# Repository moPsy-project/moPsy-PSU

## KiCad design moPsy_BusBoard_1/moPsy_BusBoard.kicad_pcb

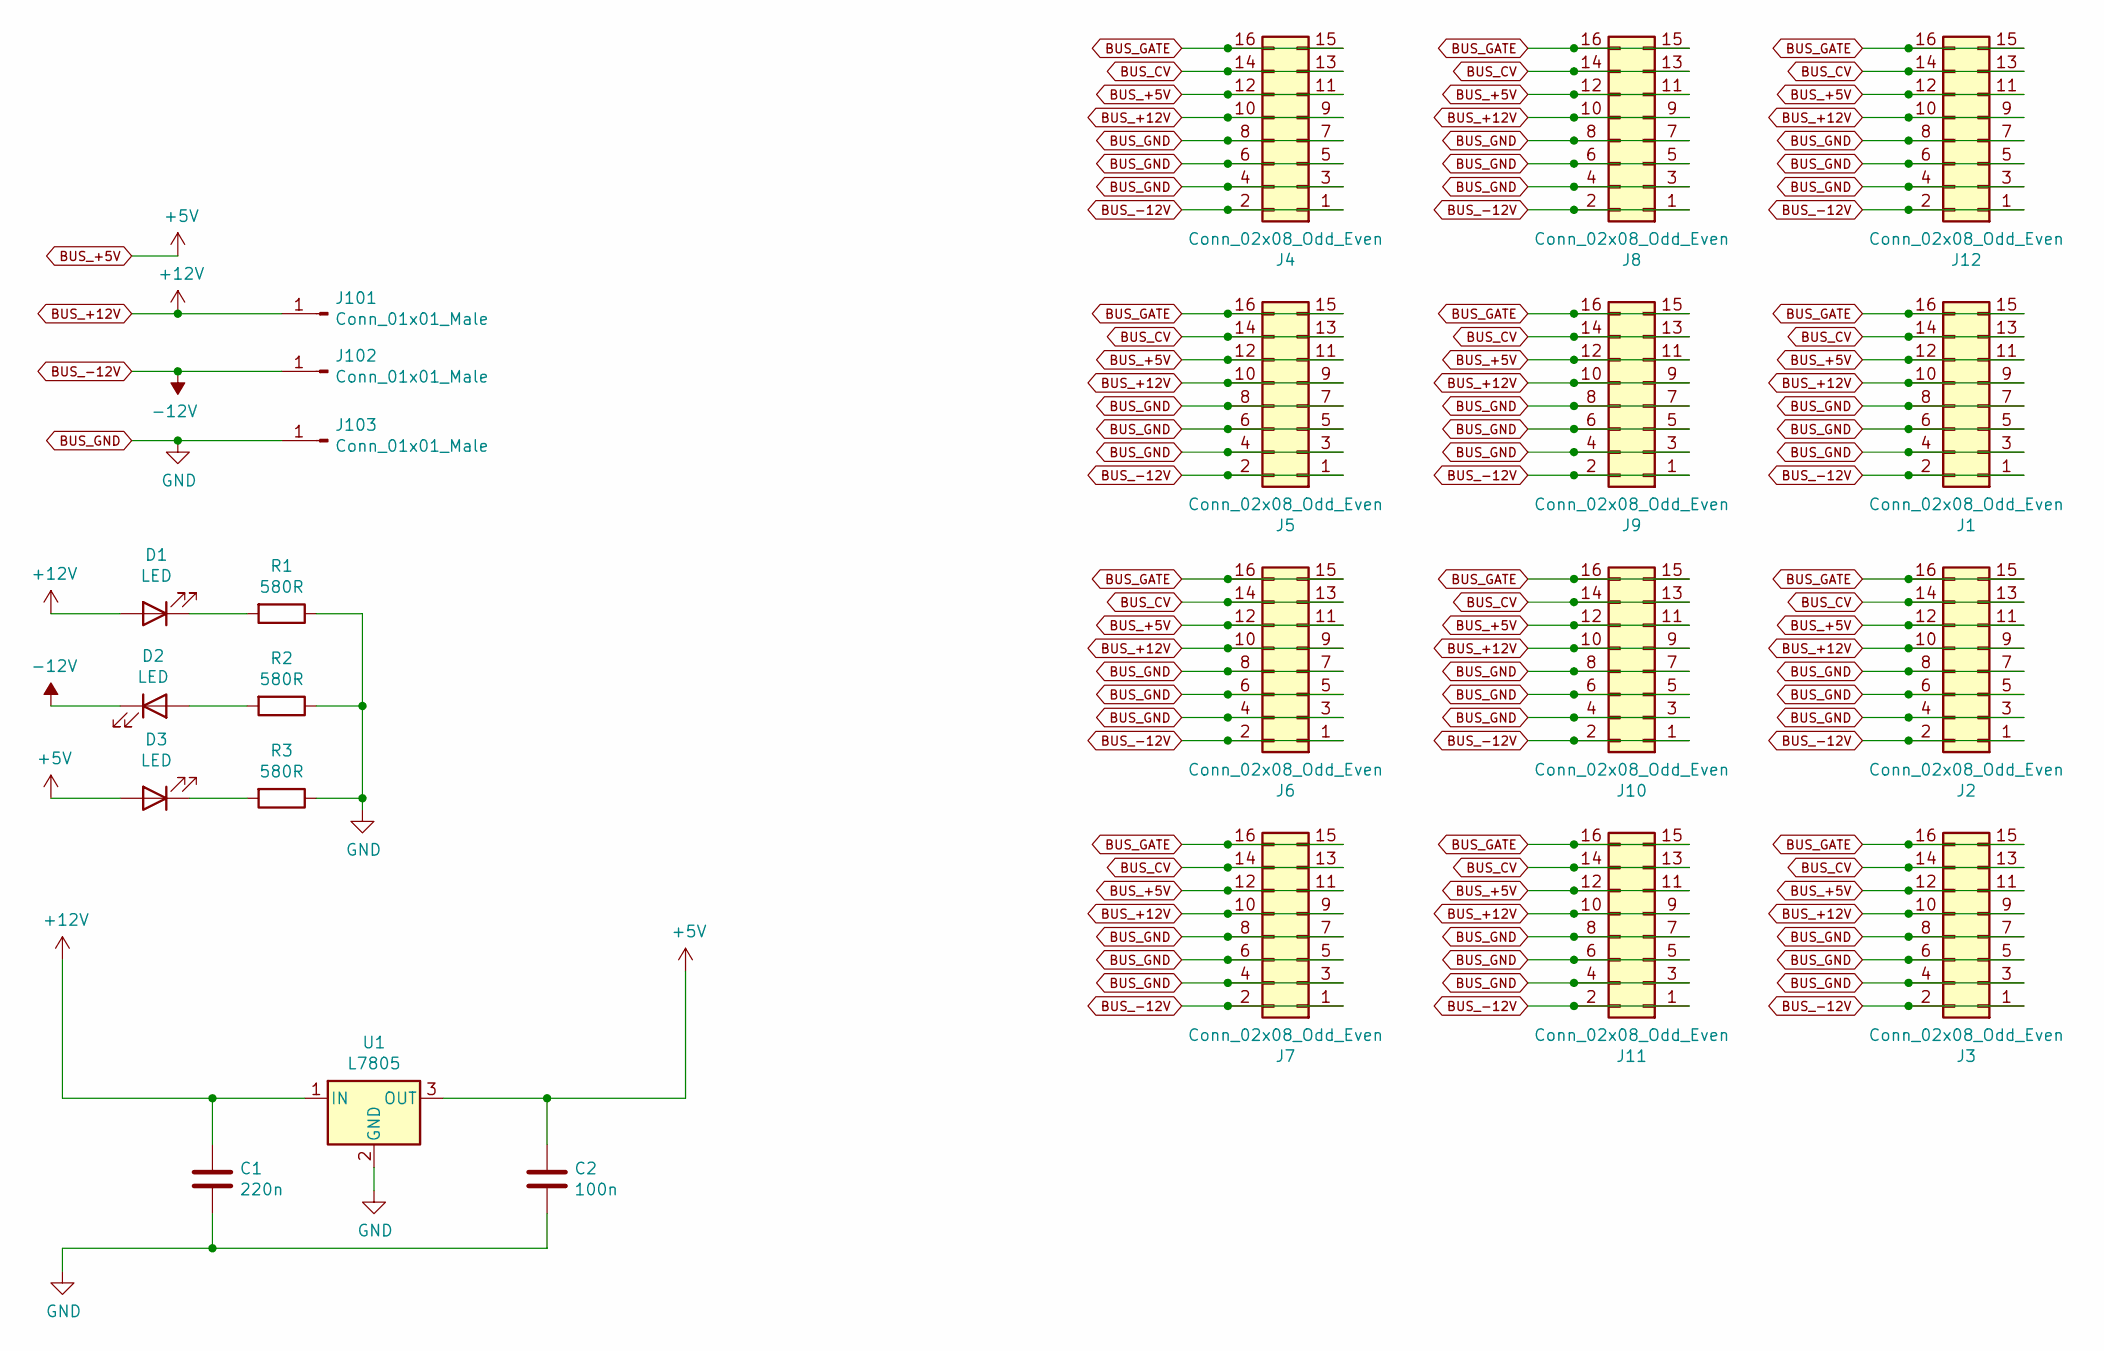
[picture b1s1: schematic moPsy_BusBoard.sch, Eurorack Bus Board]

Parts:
C1: 220n; CP_Radial_D5.0mm_P2.50mm
C2: 100n; C_Rect_L4.0mm_W2.5mm_P2.50mm
D1, D2, D3: LED; LED_D3.0mm
J1, J2, J3, J4, J5, J6, J7, J8, J9, J10, J11, J12: Conn_02x08_Odd_Even; PinHeader_2x08_P2.54mm_Vertical
J101, J102, J103: Conn_01x01_Male; Connector FS-P475
R1, R2, R3: 580R; R_Axial_DIN0207_L6.3mm_D2.5mm_P7.62mm_Horizontal
U1: L7805; TO-220-3_Horizontal_TabDown

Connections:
BUS_+5V: C2.1, D3.2 (A), J1.11, J1.12, J2.11, J2.12, J3.11, J3.12, J4.11, J4.12, J5.11, J5.12, J6.11, J6.12, J7.11, J7.12, J8.11, J8.12, J9.11, J9.12, J10.11, J10.12, J11.11, J11.12, J12.11, J12.12, U1.3 (OUT)
BUS_+12V: C1.1, D1.2 (A), J1.9, J1.10, J2.9, J2.10, J3.9, J3.10, J4.9, J4.10, J5.9, J5.10, J6.9, J6.10, J7.9, J7.10, J8.9, J8.10, J9.9, J9.10, J10.9, J10.10, J11.9, J11.10, J12.9, J12.10, J101.1, U1.1 (IN)
BUS_-12V: D2.1 (K), J1.1, J1.2, J2.1, J2.2, J3.1, J3.2, J4.1, J4.2, J5.1, J5.2, J6.1, J6.2, J7.1, J7.2, J8.1, J8.2, J9.1, J9.2, J10.1, J10.2, J11.1, J11.2, J12.1, J12.2, J102.1
BUS_CV: J1.13, J1.14, J2.13, J2.14, J3.13, J3.14, J4.13, J4.14, J5.13, J5.14, J6.13, J6.14, J7.13, J7.14, J8.13, J8.14, J9.13, J9.14, J10.13, J10.14, J11.13, J11.14, J12.13, J12.14
BUS_GATE: J1.15, J1.16, J2.15, J2.16, J3.15, J3.16, J4.15, J4.16, J5.15, J5.16, J6.15, J6.16, J7.15, J7.16, J8.15, J8.16, J9.15, J9.16, J10.15, J10.16, J11.15, J11.16, J12.15, J12.16
BUS_GND: C1.2, C2.2, J1.3, J1.4, J1.5, J1.6, J1.7, J1.8, J2.3, J2.4, J2.5, J2.6, J2.7, J2.8, J3.3, J3.4, J3.5, J3.6, J3.7, J3.8, J4.3, J4.4, J4.5, J4.6, J4.7, J4.8, J5.3, J5.4, J5.5, J5.6, J5.7, J5.8, J6.3, J6.4, J6.5, J6.6, J6.7, J6.8, J7.3, J7.4, J7.5, J7.6, J7.7, J7.8, J8.3, J8.4, J8.5, J8.6, J8.7, J8.8, J9.3, J9.4, J9.5, J9.6, J9.7, J9.8, J10.3, J10.4, J10.5, J10.6, J10.7, J10.8, J11.3, J11.4, J11.5, J11.6, J11.7, J11.8, J12.3, J12.4, J12.5, J12.6, J12.7, J12.8, J103.1, R1.1, R2.1, R3.1, U1.2 (GND)
unnamed: D1.1 (K), R1.2
unnamed: D2.2 (A), R2.2
unnamed: D3.1 (K), R3.2

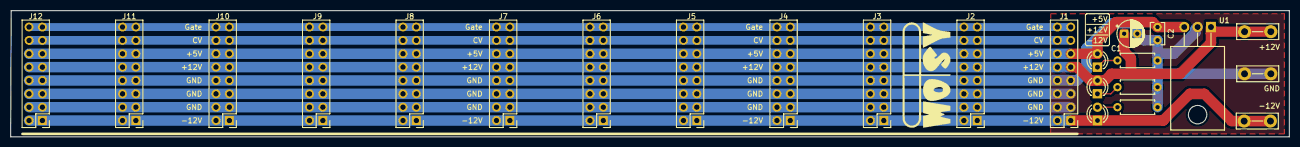
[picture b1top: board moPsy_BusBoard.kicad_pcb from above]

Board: 2 copper layers, 243.2 x 24.0 mm, 25 parts (0 on the bottom side), 9 nets.

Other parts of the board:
Ref**: Val**; moPsy_logo_kicad_20x09_FSilk

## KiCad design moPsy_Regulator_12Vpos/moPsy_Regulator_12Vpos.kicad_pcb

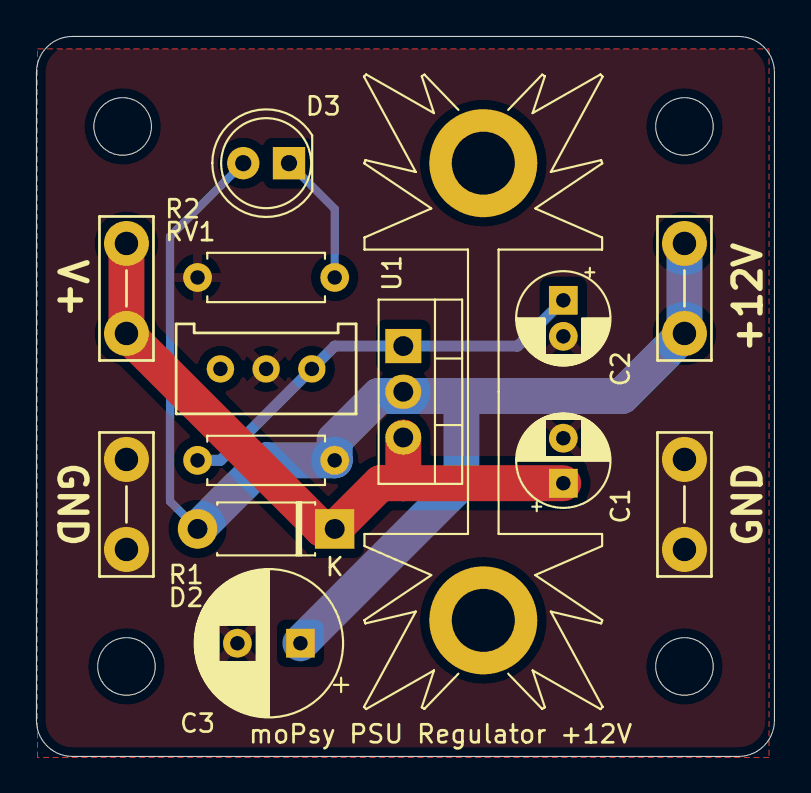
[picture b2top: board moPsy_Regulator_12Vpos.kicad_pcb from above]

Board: 2 copper layers, 41.0 x 40.0 mm, 14 parts (1 on the bottom side), 5 nets.

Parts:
C1: 10u; CP_Radial_D5.0mm_P2.50mm
C2: 25u; CP_Radial_D5.0mm_P2.00mm
C3: 150u; CP_Radial_D8.0mm_P3.50mm
D2: 1N4002; D_DO-41_SOD81_P7.62mm_Horizontal
D3: rt; LED_D5.0mm
J1, J2, J3, J4: Conn_01x01_Male; Connector FS-P475
R1: 100R; R_Axial_DIN0207_L6.3mm_D2.5mm_P7.62mm_Horizontal
R2: 480R; R_Axial_DIN0207_L6.3mm_D2.5mm_P7.62mm_Horizontal
RV1: 1k; Suntan 3296 Trim Pot
Ref**: Val**; moPsy_logo_kicad_20x09_FSilk
U1: LT1084-ADJ; TO-220-3_Vertical

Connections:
+12V: C3.1, D2.2, D3.2, J3.1, R1.1, U1.2
+VDC: C1.1, D2.1, J1.1, U1.3
GND: C1.2, C2.2, C3.2, J2.1, J4.1, R2.2, RV1.2
unnamed: C2.1, R1.2, RV1.1, U1.1
unnamed: D3.1, R2.1

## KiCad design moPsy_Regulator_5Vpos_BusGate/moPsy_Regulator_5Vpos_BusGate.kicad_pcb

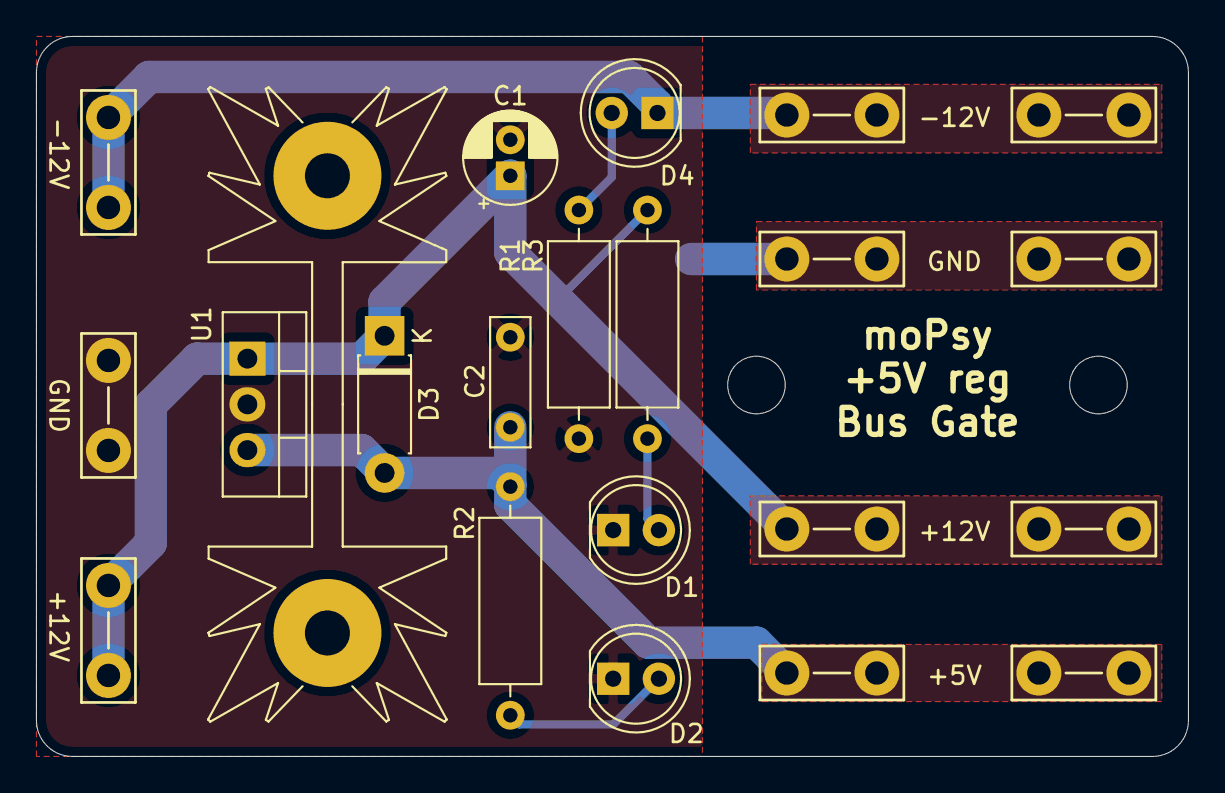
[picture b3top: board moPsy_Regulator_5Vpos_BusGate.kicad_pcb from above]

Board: 2 copper layers, 64.0 x 40.0 mm, 21 parts (0 on the bottom side), 7 nets.

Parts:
C1: 10u; CP_Radial_D5.0mm_P2.00mm
C2: 100n; C_Rect_L7.0mm_W2.0mm_P5.00mm
D1: ye; LED_D5.0mm
D2: rd; LED_D5.0mm
D3: 1N4001; D_DO-41_SOD81_P7.62mm_Horizontal
D4: bl; LED_D5.0mm
J1, J2, J3, J5, J7, J9, J11, J13, J15, J18, J19: Conn_01x01_Male; Connector FS-P475
R1, R2, R3: 520; R_Axial_DIN0309_L9.0mm_D3.2mm_P12.70mm_Horizontal
U1: L7805; TO-220-3_Vertical

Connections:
+5V: C2.1, D3.2, J9.1, J11.1, R2.1, U1.3
+12V: C1.1, D3.1, J1.1, J5.1, J7.1, R1.1, U1.1
-12V: D4.1, J3.1, J13.1, J15.1
GND: C1.2, C2.2, D1.1, D2.1, J2.1, J18.1, J19.1, R3.1, U1.2
unnamed: D1.2, R1.2
unnamed: D2.2, R2.2
unnamed: D4.2, R3.2
